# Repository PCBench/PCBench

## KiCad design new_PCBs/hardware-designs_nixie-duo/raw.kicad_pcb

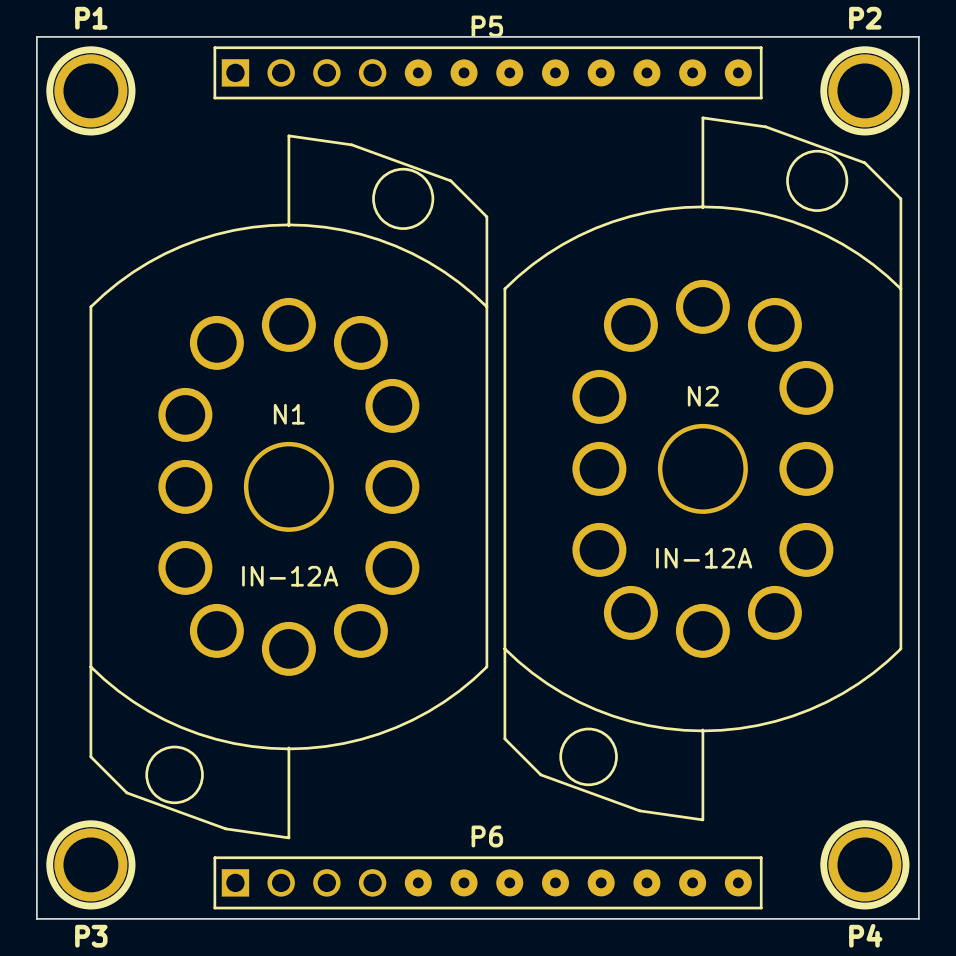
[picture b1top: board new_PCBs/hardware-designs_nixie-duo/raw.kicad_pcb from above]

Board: 2 copper layers, 49.0 x 49.0 mm, 8 parts (0 on the bottom side), 23 nets, no tracks yet.

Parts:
N1, N2: IN-12A
P1, P2, P3, P4: CONN_1; 1pin
P5, P6: CONN_12; PIN_ARRAY_12x1

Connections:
/A0: N1.2, P5.2
/A1: N1.11, P5.3
/A2: N1.10, P5.11
/A3: N1.9, P5.8
/A4: N1.8, P5.5
/A5: N1.7, P5.4
/A6: N1.6, P5.6
/A7: N1.5, P5.7
/A8: N1.4, P5.9
/A9: N1.3, P5.10
/B0: N2.2, P6.1
/B1: N2.11, P6.2
/B2: N2.10, P6.11
/B3: N2.9, P6.8
/B4: N2.8, P6.4
/B5: N2.7, P6.3
/B6: N2.6, P6.6
/B7: N2.5, P6.7
/B8: N2.4, P6.9
/B9: N2.3, P6.10
GND: P5.12, P6.5
unnamed: N2.1, P6.12
unnamed: N1.1, P5.1

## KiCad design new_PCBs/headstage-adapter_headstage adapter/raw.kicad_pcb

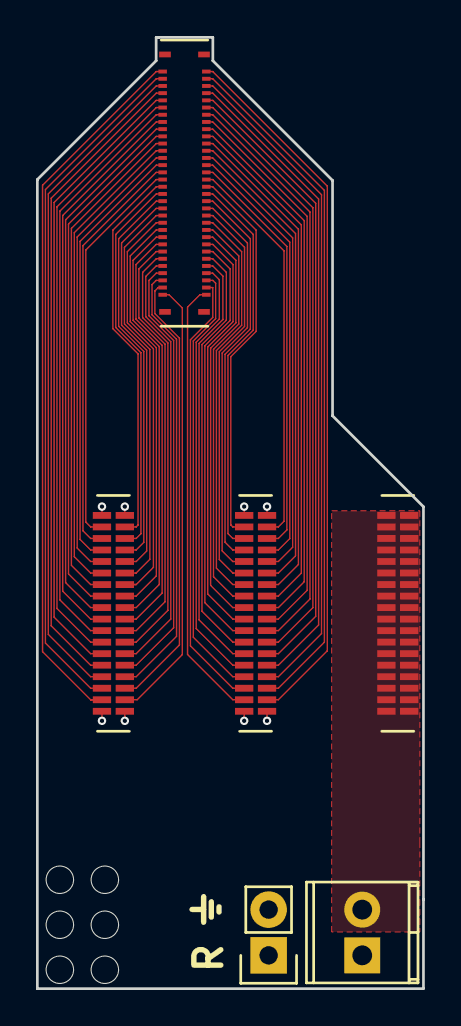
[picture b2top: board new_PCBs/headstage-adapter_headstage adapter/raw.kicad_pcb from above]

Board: 4 copper layers, 21.4 x 52.8 mm, 12 parts (0 on the bottom side), 66 nets.

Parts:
JP1: Jumper_NO_Small; Socket_Strip_Straight_1x02
M1, M2, M3, M4, M5, M6: #0 drill hole; #0_drill_hole
P1: 502426-6410; Molex_SlimStack_receptacle_64_0.4mm_pitch
P2: 1725656; TerminalBlock_Pheonix_MPT-2.54mm_2pol
U1, U2, U3: A79026-001; omnetics_connector_36_pin

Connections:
/1: P1.63, U1.3
/2: P1.1, U1.4
/3: P1.61, U1.5
/4: P1.3, U1.6
/5: P1.59, U1.7
/6: P1.5, U1.8
/7: P1.57, U1.9
/8: P1.7, U1.10
/9: P1.55, U1.11
/10: P1.9, U1.12
/11: P1.53, U1.13
/12: P1.11, U1.14
/13: P1.51, U1.15
/14: P1.13, U1.16
/15: P1.49, U1.17
/16: P1.15, U1.18
/17: P1.47, U1.19
/18: P1.17, U1.20
/19: P1.45, U1.21
/20: P1.19, U1.22
/21: P1.43, U1.23
/22: P1.21, U1.24
/23: P1.41, U1.25
/24: P1.23, U1.26
/25: P1.39, U1.27
/26: P1.25, U1.28
/27: P1.37, U1.29
/28: P1.27, U1.30
/29: P1.35, U1.31
/30: P1.29, U1.32
/31: P1.33, U1.33
/32: P1.31, U1.34
/33: P1.2, U2.3
/34: P1.64, U2.4
/35: P1.4, U2.5
/36: P1.62, U2.6
/37: P1.6, U2.7
/38: P1.60, U2.8
/39: P1.8, U2.9
/40: P1.58, U2.10
/41: P1.10, U2.11
/42: P1.56, U2.12
/43: P1.12, U2.13
/44: P1.54, U2.14
/45: P1.14, U2.15
/46: P1.52, U2.16
/47: P1.16, U2.17
/48: P1.50, U2.18
/49: P1.18, U2.19
/50: P1.48, U2.20
/51: P1.20, U2.21
/52: P1.46, U2.22
/53: P1.22, U2.23
/54: P1.44, U2.24
/55: P1.24, U2.25
/56: P1.42, U2.26
/57: P1.26, U2.27
/58: P1.40, U2.28
/59: P1.28, U2.29
/60: P1.38, U2.30
/61: P1.30, U2.31
/62: P1.36, U2.32
/63: P1.32, U2.33
/64: P1.34, U2.34
/G: JP1.2, P2.2, U1.1, U1.36, U2.1, U2.36, U3.1, U3.2, U3.3, U3.4, U3.5, U3.6, U3.7, U3.8, U3.9, U3.10, U3.11, U3.12, U3.13, U3.14, U3.15, U3.16, U3.17, U3.18, U3.19, U3.20, U3.21, U3.22, U3.23, U3.24, U3.25, U3.26, U3.27, U3.28, U3.29, U3.30, U3.31, U3.32, U3.33, U3.34, U3.35, U3.36
/R: JP1.1, P2.1, U1.2, U1.35, U2.2, U2.35

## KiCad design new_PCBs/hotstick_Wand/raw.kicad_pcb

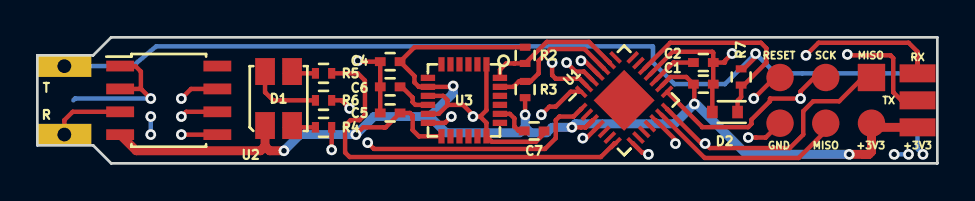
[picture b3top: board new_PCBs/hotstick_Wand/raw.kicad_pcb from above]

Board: 4 copper layers, 50.0 x 7.0 mm, 20 parts (1 on the bottom side), 24 nets.

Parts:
C1, C2, C4, C6: 100n; C_0402
C5: 10n; C_0402
C7: 2.2n; C_0402
D1: ASMB-MTB0-0A3A2; Tri-Colour_LED
D2: 3V3; SOD-523
P1: ISP; ISP_pads_2x3
P2: KLB4; Jack_3.5mm_KLB
P3: BASE; Base_Connector
R2, R3: 10k; R_0402
R4: 68R; R_0402
R5, R6: 10R; R_0402
R7: 10K; R_0402
U1: ATMEGA328-MMH; QFN-28-1EP_4x4mm_Pitch0.45mm
U2: MAX31855KASA+; SOIC-8_3.9x4.9mm_Pitch1.27mm
U3: MPU-6050

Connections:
+3V3: C1.1, C4.2, C5.2, D1.1, P1.2, P3.1, R2.1, R3.1, U1.3, U1.16, U2.4, U3.8, U3.13
/HEAT: P2.T, P3.2, R7.1
/HEAT_DETECT: D2.1, R7.2, U1.19
/LED_B: R6.1, U1.8
/LED_G: R5.1, U1.7
/LED_R: R4.1, U1.1
/MISO: P1.1, U1.14, U2.7
/MOSI: P1.4, U1.13
/MPU_INT: U1.28, U3.12
/RESET: P1.5, U1.25
/RX: P3.3, U1.26
/SCK: P1.3, U1.15, U2.5
/SCL: R3.2, U1.24, U3.23
/SDA: R2.2, U1.23, U3.24
/SENS: P2.R, U2.3
/TIP_TEMP_SELECT: U1.12, U2.6
/TX: P3.4, U1.27
GND: C1.2, C2.2, C4.1, C5.1, C6.1, C7.1, D2.2, P1.6, P2.S, P3.5, U1.4, U1.18, U2.1, U2.2, U3.1, U3.9, U3.11, U3.18
unnamed: C2.1, U1.17
unnamed: C6.2, U3.10
unnamed: C7.2, U3.20
unnamed: D1.2, R6.2
unnamed: D1.3, R5.2
unnamed: D1.4, R4.2

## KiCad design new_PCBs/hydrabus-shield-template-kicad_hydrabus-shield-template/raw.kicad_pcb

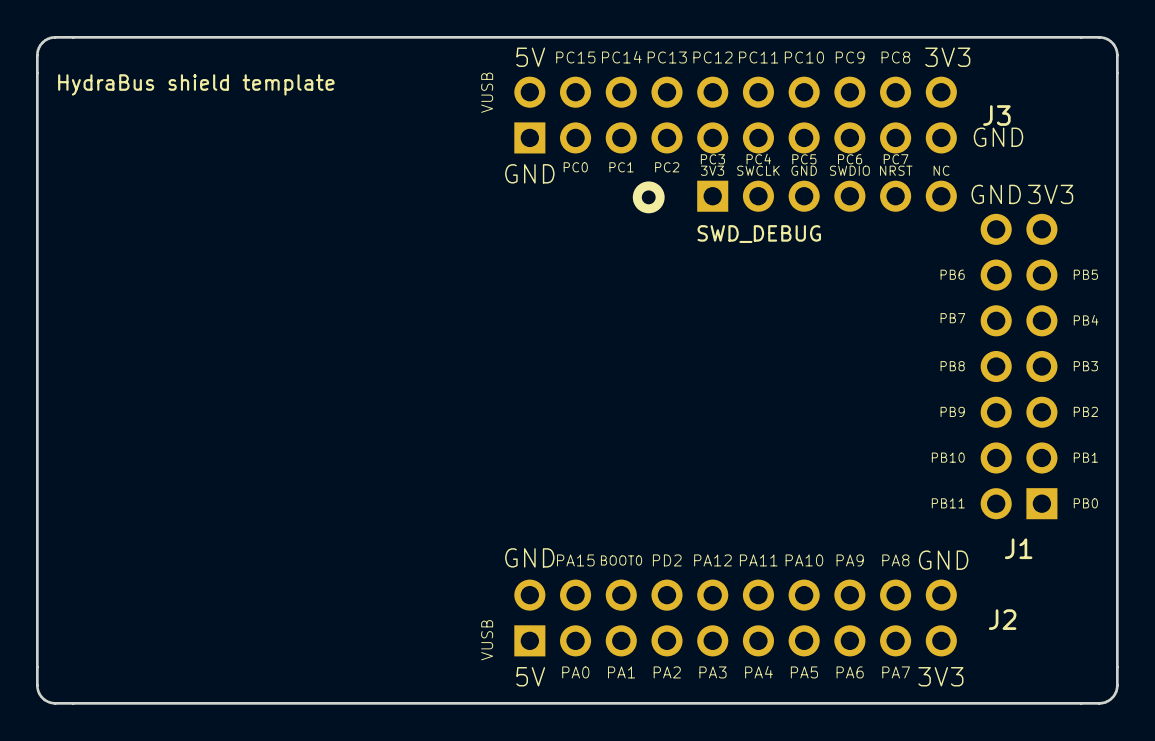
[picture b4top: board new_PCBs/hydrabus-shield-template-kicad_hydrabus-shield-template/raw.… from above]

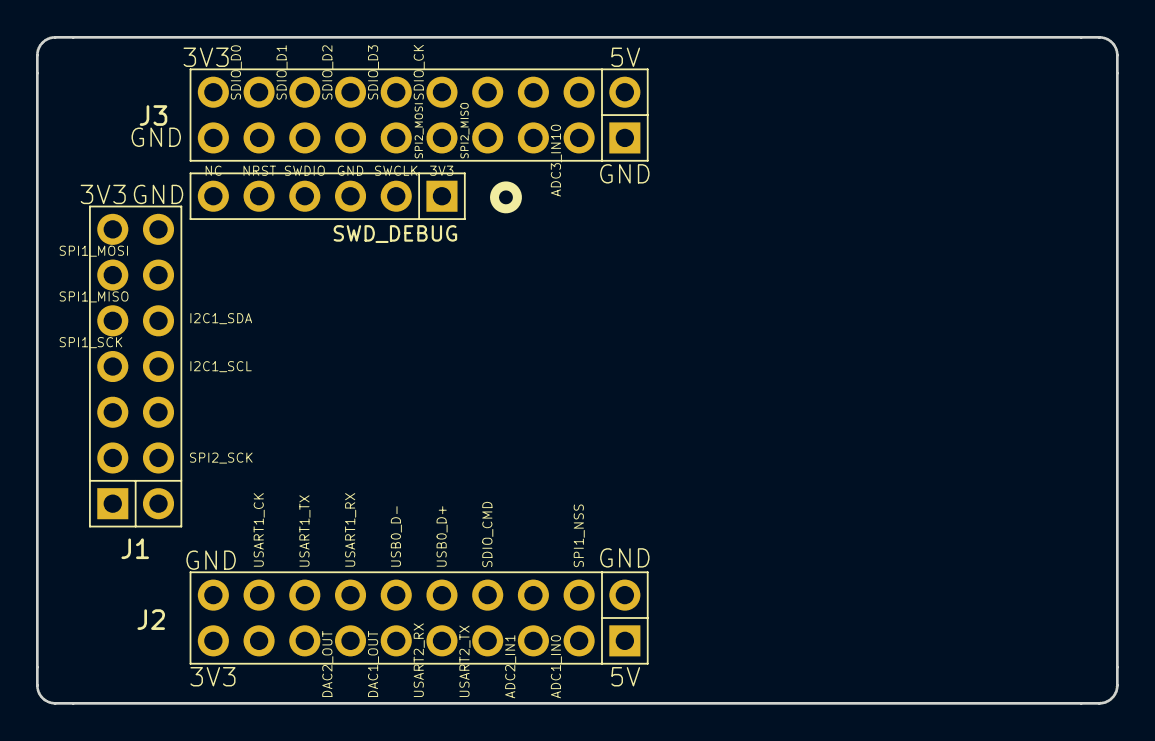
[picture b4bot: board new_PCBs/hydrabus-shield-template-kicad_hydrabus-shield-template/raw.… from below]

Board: 2 copper layers, 60.0 x 37.0 mm, 4 parts (4 on the bottom side), 3 nets, no tracks yet.

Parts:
J1: CONN_02X07; Hydrabus_Shield_Conn_2x07
J2, J3: CONN_02X10; Hydrabus_Shield_Conn_2x10
J4: CONN_01X06; Hydrabus_Shield_Conn_1x06

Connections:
+3V3: J1.13, J2.19, J3.20, J4.1
+5V: J2.1, J3.2
GND: J1.14, J2.2, J2.20, J3.1, J3.19, J4.3

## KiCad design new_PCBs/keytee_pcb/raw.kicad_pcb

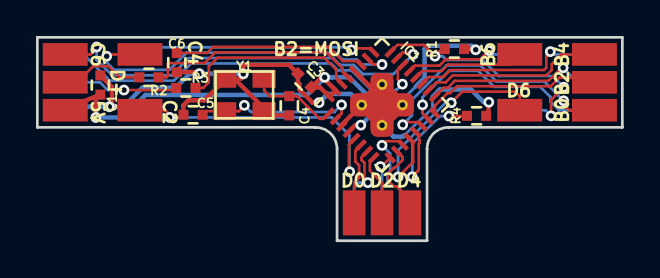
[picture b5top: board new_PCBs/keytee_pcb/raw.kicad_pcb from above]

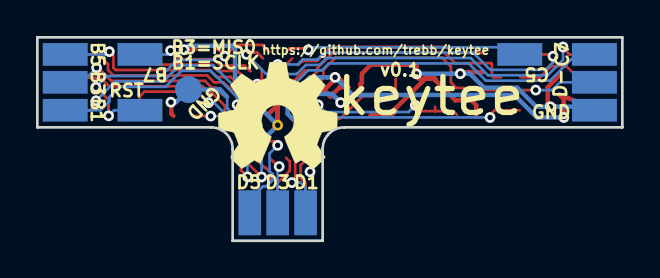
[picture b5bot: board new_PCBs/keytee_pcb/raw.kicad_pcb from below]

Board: 2 copper layers, 32.5 x 11.3 mm, 37 parts (13 on the bottom side), 31 nets.

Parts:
C1, C6: 1u; C_0402_square
C3: 100n; C_0402_square
C4, C5: 18p; C_0402_square
IC1: ATMEGA32U2; QFN-32-1EP_5x5mm_Pitch0.5mm_internal_vias
R1, R4: 10k; R_0402_square
R2, R3: 22; R_0402_square
W0, W1, W2, W3, W4, W5, W6, W7, W8, W15, W16, W17, W18, W19, W20, W21, W22, W23, W24, W25, W26, W27, W28, W29, W30: TEST_1P; SolderWirePad_SMD
W31: TEST_1P; SolderWirePad_SMD_circular
Y1: MT 16MHz; crystal_MT_32x25

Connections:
/B0: IC1.14, W0.1
/B1: IC1.15, W1.1
/B2: IC1.16, W2.1
/B3: IC1.17, W3.1
/B4: IC1.18, W15.1
/B5: IC1.19, W16.1
/B6: IC1.20, W17.1
/B7: IC1.21, W18.1
/C2: IC1.5, W26.1
/C4: IC1.26, W27.1
/C5: IC1.25, W28.1
/C6: IC1.23, W29.1
/C7: IC1.22, W30.1
/D0: IC1.6, W19.1
/D1: IC1.7, W20.1
/D2: IC1.8, W21.1
/D3: IC1.9, W22.1
/D4: IC1.10, W23.1
/D5: IC1.11, W24.1
/D6: IC1.12, W25.1
GND: C1.2, C3.2, C4.2, C5.2, C6.1, IC1.3, IC1.28, IC1.33, R4.1, W7.1, W31.1, Y1.3
unnamed: C4.1, IC1.1, Y1.1
unnamed: C5.1, IC1.2, Y1.2
unnamed: C6.2, IC1.27
unnamed: IC1.13, R4.2
unnamed: IC1.24, R1.2, W8.1
unnamed: IC1.29, R2.1
unnamed: IC1.30, R3.1
unnamed: R2.2, W4.1
unnamed: R3.2, W5.1
VCC: C1.1, C3.1, IC1.4, IC1.31, IC1.32, R1.1, W6.1

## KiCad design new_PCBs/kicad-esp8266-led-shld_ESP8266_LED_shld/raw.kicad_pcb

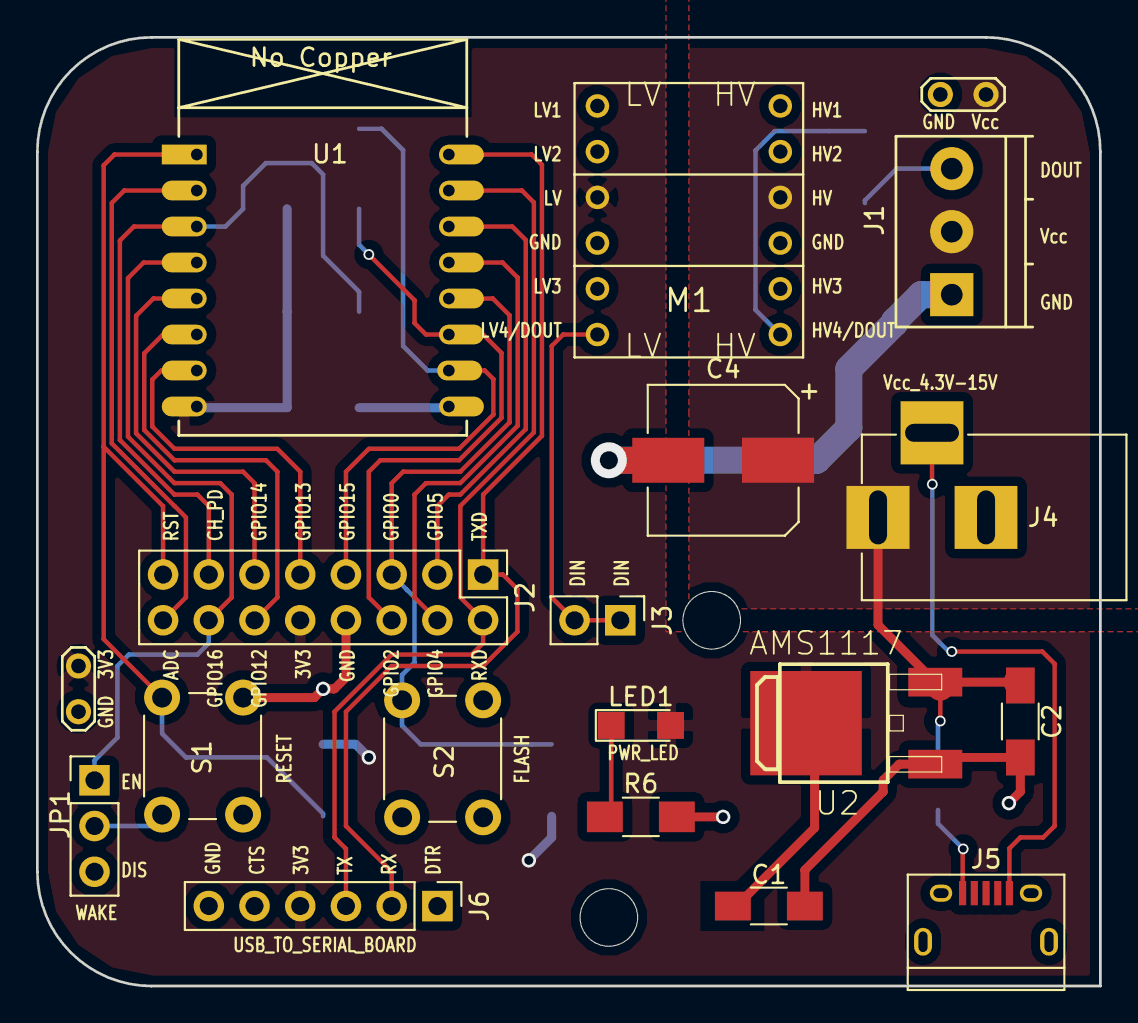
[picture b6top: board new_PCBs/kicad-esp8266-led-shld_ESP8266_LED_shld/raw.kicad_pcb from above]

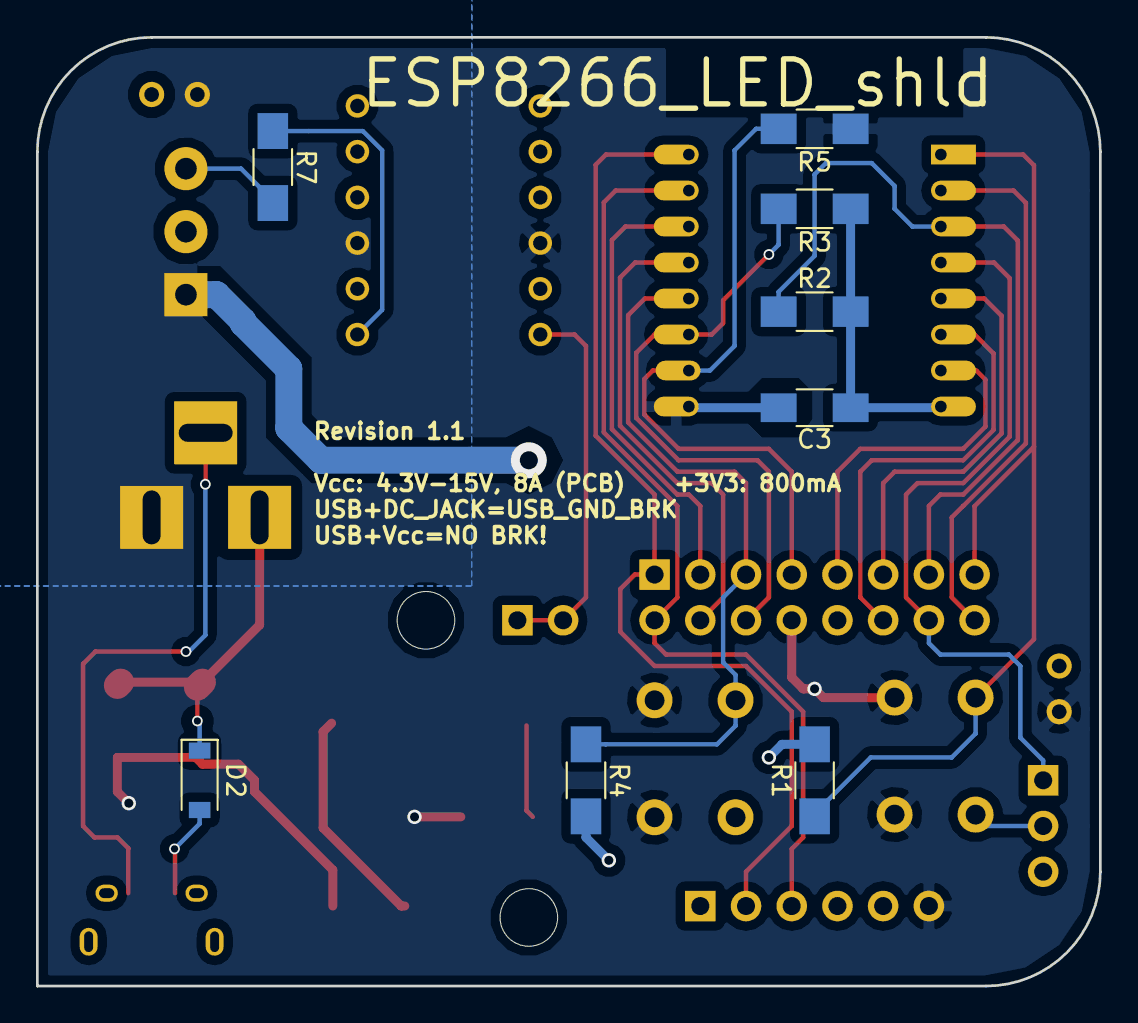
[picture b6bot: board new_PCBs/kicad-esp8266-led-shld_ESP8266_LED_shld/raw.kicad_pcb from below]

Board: 2 copper layers, 59.1 x 52.7 mm, 29 parts (8 on the bottom side), 23 nets.

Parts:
C1, C2, C3: 220uF; C_1206_HandSoldering
C4: 470uF; CP_Elec_8x10
D2: DIODE; D_SOD-123
J1: Pwr_Dat_Out; TerminalBlock_Pheonix_PT-3.5mm_3pol
J2: CONN_02X08; Pin_Header_Straight_2x08_Pitch2.54mm
J3: CONN_DIN; Pin_Header_Straight_1x02_Pitch2.54mm
J4: BARREL_JACK
J5: USB-MICROB; USB_Micro-B-revision2
J6: CONN_01X06; Pin_Header_Straight_1x06_Pitch2.54mm
JP1: Jumper; Pin_Header_Straight_1x03_Pitch2.54mm
LED1: LED1206; LED_1206
M1: LOGIC_LEVEL_CONVERTER; LOGIC_LEVEL_CONVERTER-revision2
MH1, MH2: MountingHole_3.2mm_M3
R1, R2, R3, R4, R5: 10K; R_1206_HandSoldering
R6: 65; R_1206_HandSoldering
R7: 1K; R_1206_HandSoldering
S1: RESET; SW_PUSH_6mm
S2: FLASH; SW_PUSH_6mm
T1, T1#2: Test_Point_2Pads
U1: ESP-07v2
U2: AMS1117; V-REG_DPACK-revision2

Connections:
+3V3: C1.1, C3.1, J2.10, J6.4, LED1.2, M1.P$3, R1.2, R2.2, R3.1, R4.2, T1#2.1, U1.8, U2.2
ADC: J2.16, U1.2
CH_PD: J2.13, R2.1, U1.3
DIN: J3.1, J3.2, M1.P$6
DOUT: J1.3, R7.2
GND: C1.2, C2.2, C3.2, C4.2, J1.1, J2.8, J4.2, J6.6, M1.P$4, M1.P$9, R5.1, R6.2, S1.2, S2.2, T1.2, T1#2.2, U1.9, U2.1
GNDBREAK: J4.3, J5.GND
GPIO0: J2.5, R4.1, S2.1, U1.12
GPIO2: J2.6, R3.2, U1.11
GPIO4: J2.4, U1.13
GPIO5: J2.3, U1.14
GPIO12: J2.12, U1.6
GPIO13: J2.9, U1.7
GPIO14: J2.11, U1.5
GPIO15: J2.7, R5.2, U1.10
GPIO16: J2.14, JP1.1, U1.4
unnamed: D2.2, J5.VBUS
unnamed: LED1.1, R6.1
unnamed: M1.P$7, R7.1
REST: J2.15, JP1.2, R1.1, S1.1, U1.1
RXD: J2.2, J6.3, U1.15
TXD: J2.1, J6.2, U1.16
Vin: C2.1, C4.1, D2.1, J1.2, J4.1, M1.P$10, T1.1, U2.3

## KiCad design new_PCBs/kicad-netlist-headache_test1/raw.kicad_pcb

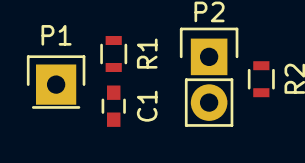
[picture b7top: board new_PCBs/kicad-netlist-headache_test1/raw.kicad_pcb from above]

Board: 2 copper layers, 5 parts (0 on the bottom side), 2 nets, no tracks yet.

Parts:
C1: C; C_0603
P1: CONN_01X01; Pin_Header_Straight_1x01
P2: CONN_01X02; Pin_Header_Straight_1x02
R1, R2: R; R_0603

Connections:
/LABEL: P2.1, P2.2, R2.1, R2.2
unnamed: C1.1, P1.1, R1.2

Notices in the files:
new_PCBs/hydrabus-shield-template-kicad_hydrabus-shield-template/raw.kicad_pcb:
CC BY-SA 4.0
